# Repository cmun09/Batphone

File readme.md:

# Batphone: Ultrasonic Microphones for Animal Recordings and Research

## Please read through before you go ahead with the microphone. Use it under your own risk. 

I developed this microphone to record ultrasonic soundwaves emitted by bio sonar from bats. 

The quick specifications:

| Specification             | Nominal   | Min                         | Max                         |
| ------------------------- | --------- | --------------------------- | --------------------------- |
| Operating Voltage (V)     | 5         | Minimum of the LDO or opamp | Maximum of the opamp or LDO |
| Frequency Range (Hz)      | 1 - 100K  | 1                           | ∞                           |
| Signal Output Voltage (V) | 0.5 - 3.3 | 0.5                         | 3.3                         |

The microphone itself has very low gain so in order to increase it, you will need to turn the potentiometer.

I have designed in this in EagleCAD. Many different PCB cad software should support or this file type. I believe there ways to export the current file but, I personally do not recommend it. EagleCAD is free with a valid .edu email at Autodesk's website.

Design of the microphone mainly relies on the Knowle's FG sensor. This sensor is rather pricey, going in the ranges for ~$25 USD. The microphones integrity has been tested against a GRAS standard microphone (Unknown model) that displayed a flat frequency response between 1 Hz- 200 kHz with -1db trailing near the end. 

My microphone that I have developed is not designed to be used as an replacement microphone for standard microphones but a portable, cheaper, and smaller alternative to the commercial ultrasonic microphones aimed at researches alike.

I thank Dr. Rolf Müeller for overseeing the project and research for his Bat bio-sonar research. 

If you have any questions, please email me at lucasmun@vt.edu.

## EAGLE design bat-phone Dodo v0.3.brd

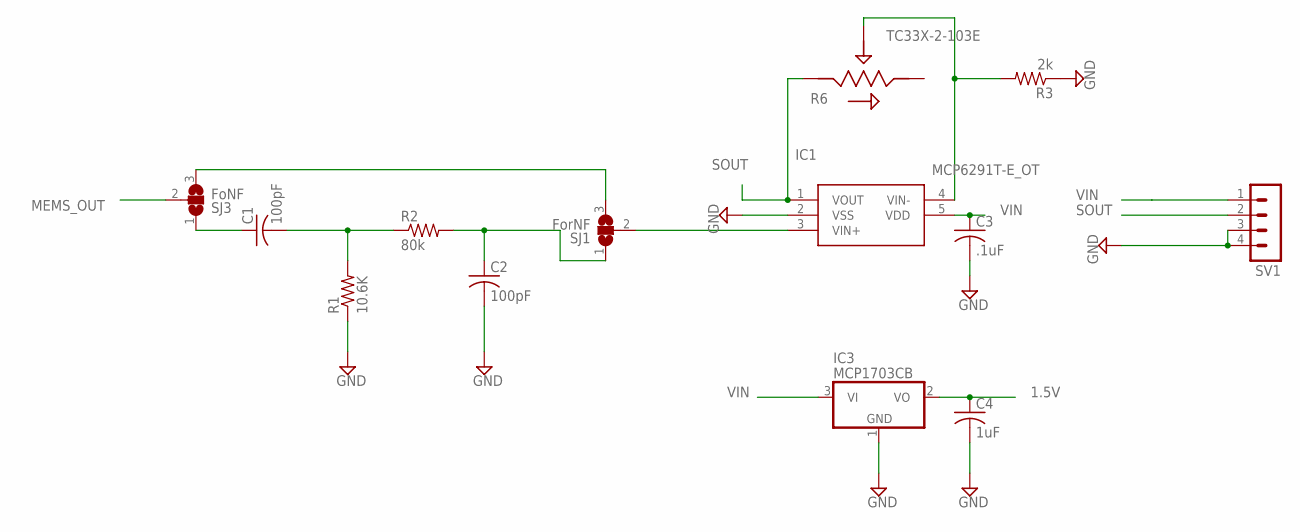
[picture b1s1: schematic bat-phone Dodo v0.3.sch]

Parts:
C1, C2: 100pF; C0603
C3: .1uF; C0603
C4: 1uF; C0603
IC1: MCP6291T-E_OT; SOT95P280X145-5N
IC3: MCP1703CB; SOT23
R1: 10.6K; R0603
R2: 80k; R0603
R3: 2k; R0603
R6: TC33X-2-103E; 35WR
SJ1: ForNF; SJ_2
SJ3: FoNF; SJ_2
SV1: MA04-1

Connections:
1.5V: C4.1, IC3.2 (VO)
GND: C2.2, C3.2, C4.2, IC1.2 (VSS), IC3.1 (GND), R1.1, R3.1, SV1.3, SV1.4
MEMS_OUT: SJ3.2
unnamed: IC1.3 (VIN+), SJ1.2
unnamed: C1.2, R1.2, R2.1
unnamed: C2.1, R2.2, SJ1.1
unnamed: IC1.4 (VIN-), R3.2, R6.2
unnamed: SJ1.3, SJ3.3
unnamed: C1.1, SJ3.1
SOUT: IC1.1 (VOUT), R6.1, SV1.2
VIN: C3.1, IC1.5 (VDD), IC3.3 (VI), SV1.1

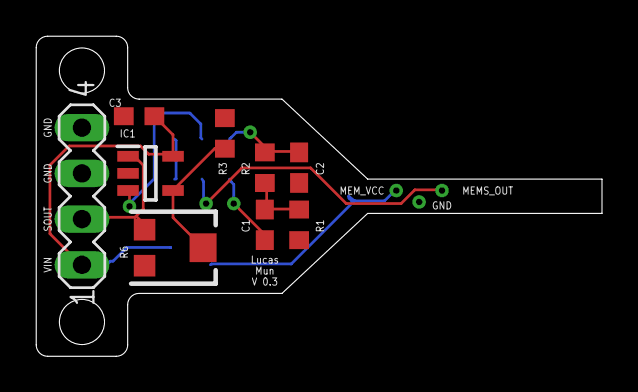
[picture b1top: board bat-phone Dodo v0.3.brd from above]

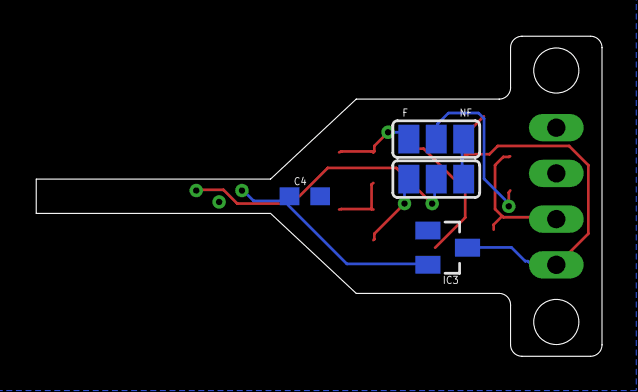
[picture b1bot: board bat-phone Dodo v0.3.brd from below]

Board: 2 copper layers, 31.4 x 17.8 mm, 13 parts (4 on the bottom side), 10 nets.

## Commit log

2019-07-20 Inital Files
2019-07-20 Updated BOM
2019-07-20 Added FFT figure
2019-07-20 Create LICENSE
2019-07-20 Added license
